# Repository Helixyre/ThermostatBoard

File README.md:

# ThermostatBoard
Projet KiCAD de la carte Thermostat SNEC 2025

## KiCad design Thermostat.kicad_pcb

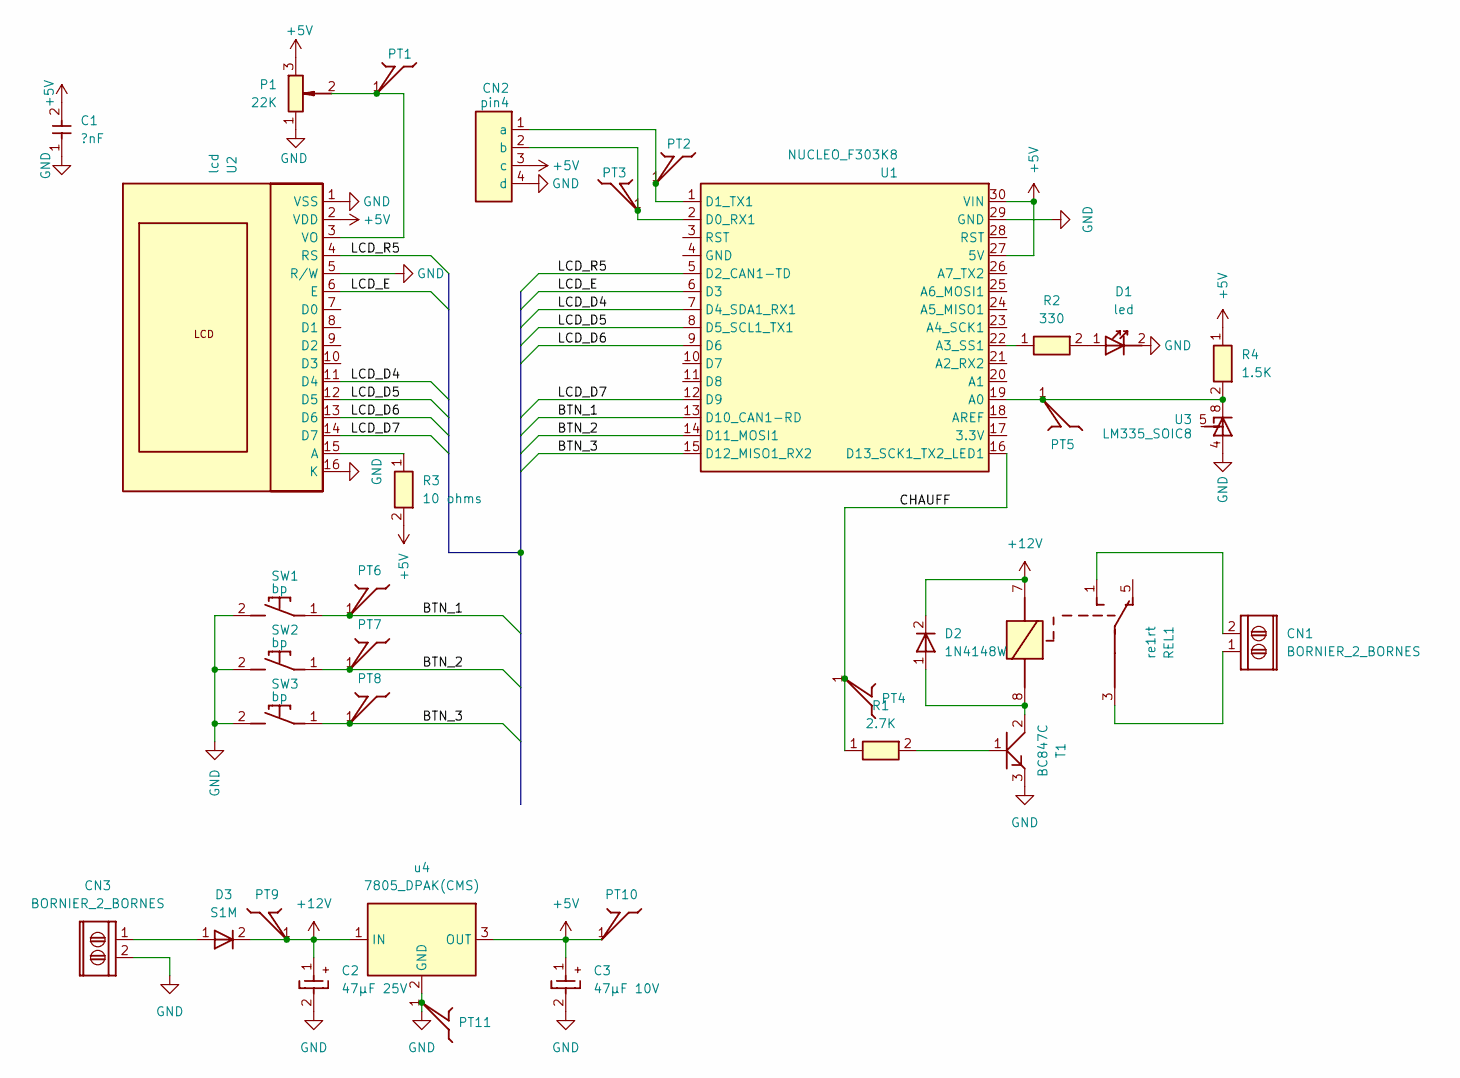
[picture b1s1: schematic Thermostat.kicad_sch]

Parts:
C1: ?nF; CMS_1206_V2
C2: 47µF 25V; CMS_2917_CPOL
C3: 47µF 10V; CMS_2917_CPOL
CN1, CN3: BORNIER_2_BORNES; BORNIER_2BR_5_08mm
CN2: pin4
D1: led; LED_5MM
D2: 1N4148W; CMS_SOD323
D3: S1M; CMS_SMA
P1: 22K; ajust_h
PT1, PT2, PT3, PT4, PT5, PT6, PT7, PT8, PT9, PT10, PT11: ptest
R1: 2.7K; CMS_1206_V2
R2: 330; CMS_1206_V2
R3: 10 ohms; CMS_1206_V2
R4: 1.5K; CMS_1206_V2
REL1: re1rt; Re1RTd
SW1, SW2, SW3: bp; BP_KSEM31G_CMS
T1: BC847C; SOT-23
U1: NUCLEO_F303K8; DIP30-600
U2: lcd; lcd_2x16_vide
U3: LM335_SOIC8; SOG.050-08-WG.275-L.250
u4: 7805_DPAK(CMS); DPAK

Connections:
+5V: C1.2, C3.1, CN2.3 (c), P1.3 (2), PT10.1, R3.2, R4.1, U1.27 (5V), U1.30 (VIN), U2.2 (VDD), u4.3 (OUT)
+12V: C2.1, D2.2 (K), D3.2 (K), PT9.1, REL1.7 (B), u4.1 (IN)
/BTN_1: PT6.1, SW1.1, U1.13 (D10_CAN1-RD)
/BTN_2: PT7.1, SW2.1, U1.14 (D11_MOSI1)
/BTN_3: PT8.1, SW3.1, U1.15 (D12_MISO1_RX2)
/CHAUFF: PT4.1, R1.1, U1.16 (D13_SCK1_TX2_LED1)
/LCD_D4: U1.7 (D4_SDA1_RX1), U2.11 (D4)
/LCD_D5: U1.8 (D5_SCL1_TX1), U2.12 (D5)
/LCD_D6: U1.9 (D6), U2.13 (D6)
/LCD_D7: U1.12 (D9), U2.14 (D7)
/LCD_E: U1.6 (D3), U2.6 (E)
/LCD_R5: U1.5 (D2_CAN1-TD), U2.4 (RS)
GND: C1.1, C2.2, C3.2, CN2.4 (d), CN3.2, D1.2 (K), P1.1, PT11.1, SW1.2, SW2.2, SW3.2, T1.3 (e), U1.29 (GND), U2.1 (VSS), U2.5 (R/W), U2.16 (K), U3.4, u4.2 (GND)
unnamed: CN1.1, REL1.3 (COM)
unnamed: CN1.2, REL1.1 (NO)
unnamed: CN2.1 (a), PT2.1, U1.1 (D1_TX1)
unnamed: CN2.2 (b), PT3.1, U1.2 (D0_RX1)
unnamed: CN3.1, D3.1 (A)
unnamed: D1.1 (A), R2.2
unnamed: D2.1 (A), REL1.8 (A), T1.2 (c)
unnamed: P1.2 (t), PT1.1, U2.3 (VO)
unnamed: PT5.1, R4.2, U1.19 (A0), U3.8
unnamed: R1.2, T1.1 (b)
unnamed: R2.1, U1.22 (A3_SS1)
unnamed: R3.1, U2.15 (A)

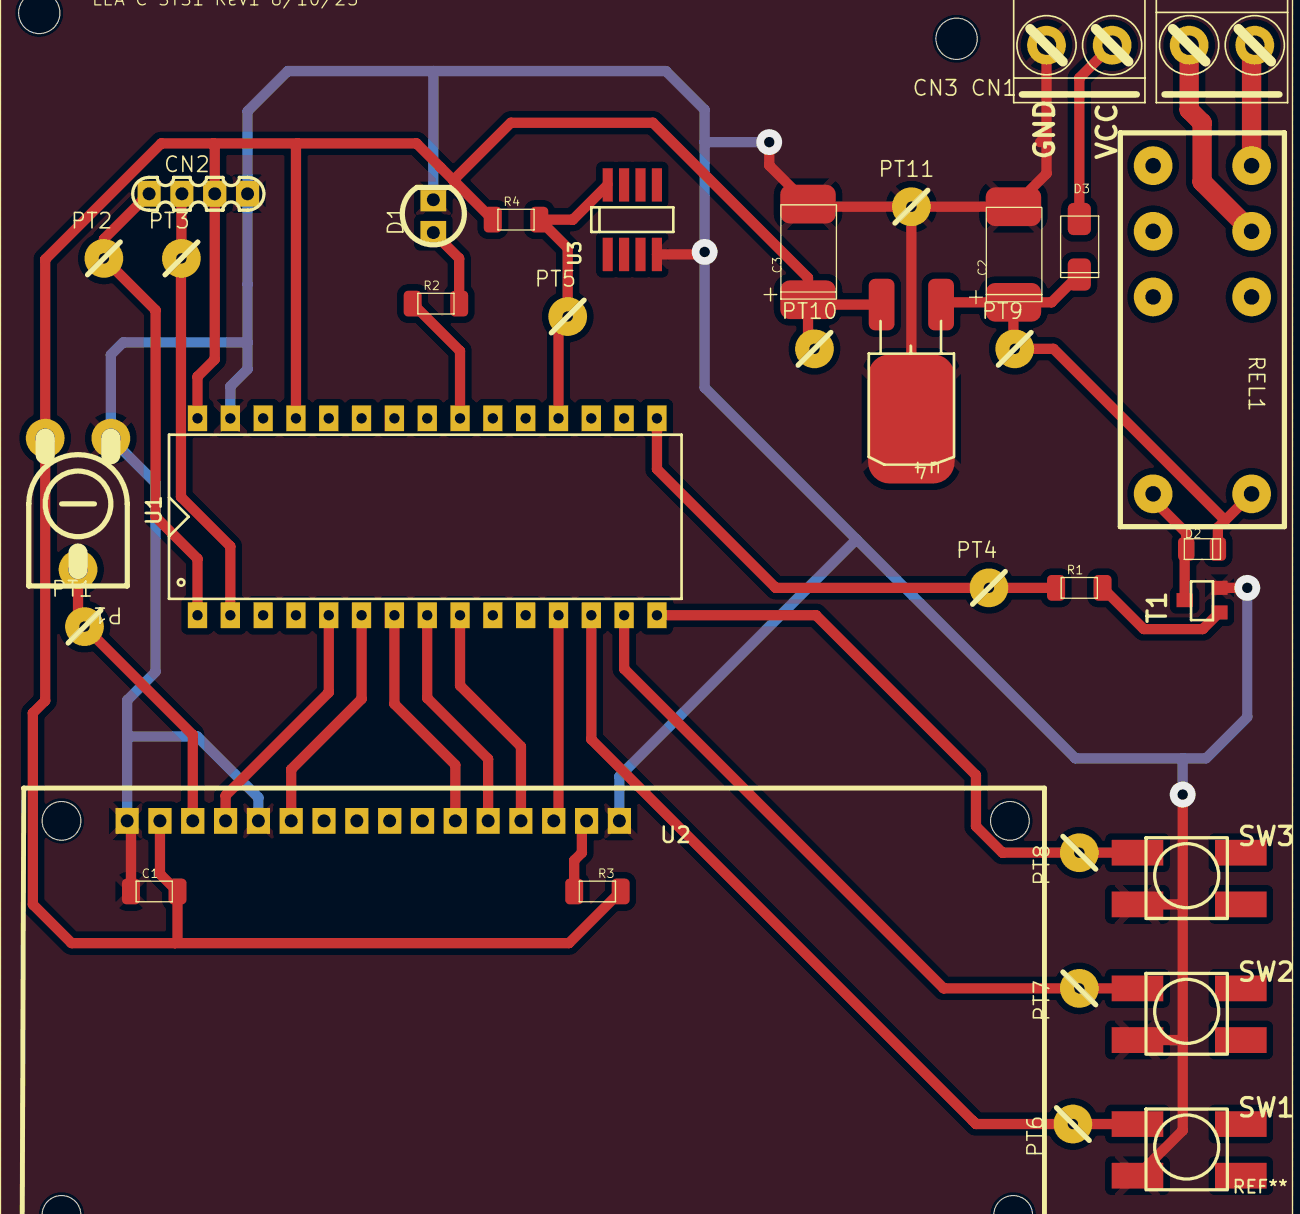
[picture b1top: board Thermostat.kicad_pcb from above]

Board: 2 copper layers, 34 parts (0 on the bottom side), 25 nets.

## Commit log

2025-10-14 Revision 1.0
2025-10-16 Add PCB image to README
    Added an image of the PCB to the README.
